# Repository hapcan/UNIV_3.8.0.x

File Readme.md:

UNIV 3.8.0.x
============

RGB LED Controller - 3 channel LED or 1 channel RGB LED controller 5A per channel @12-24V for DIN rail

Device webpage: http://hapcan.com/devices/universal/univ_3/univ_3-8-0-x/

Hardware created in Eagle PCB Software http://www.cadsoftusa.com/

Firmware created in Microchip MPLAB http://www.microchip.com/mplabide/ in assembly language

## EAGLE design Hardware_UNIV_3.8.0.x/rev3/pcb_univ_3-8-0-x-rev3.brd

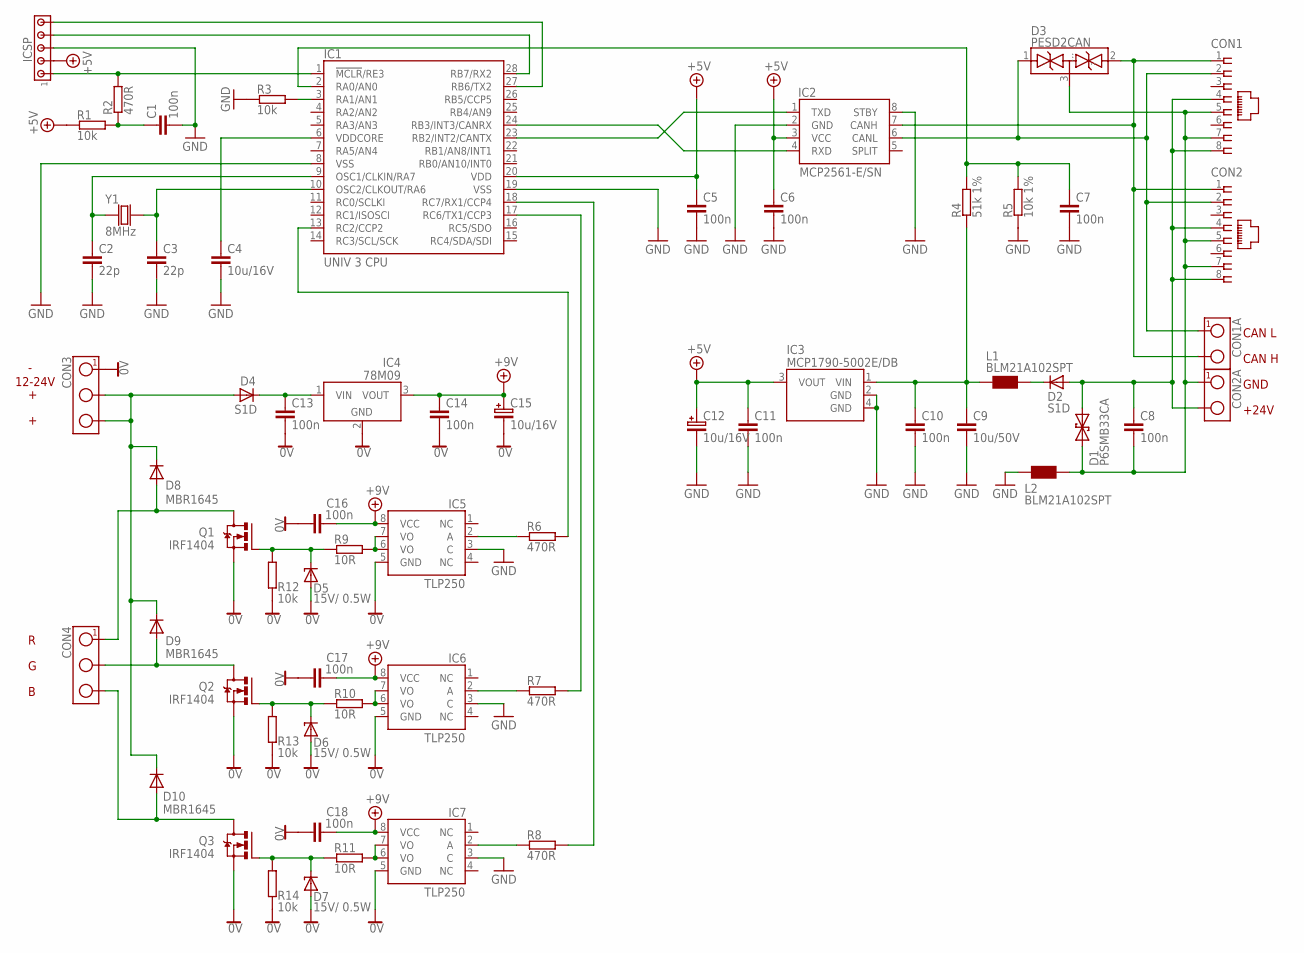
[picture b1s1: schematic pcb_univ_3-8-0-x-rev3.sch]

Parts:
C1, C5, C6, C7, C8, C10, C11, C13, C14, C16, C17, C18: 100n; 0805
C2, C3: 22p; 0805
C4: 10u/16V; 0805
C9: 10u/50V; 1210
C12, C15: 10u/16V; SMC_B
CON1, CON2: RJ45-SOCKET; RJ45-PCB-SOCKET
CON1A, CON2A: TERMINAL-2; ARK2-5X10,5MM
CON3, CON4: TERMINAL-3; ARK3-5X10.5MM
D1: P6SMB33CA; DO-214_TRANSIL2
D2, D4: S1D; DO-214
D3: PESD2CAN; SOT-23
D5, D6, D7: 15V/ 0.5W; SOD-80
D8, D9, D10: MBR1645; TO220V-2
IC1: UNIV 3 CPU; UNIV3CPU
IC2: MCP2561-E/SN; SO-08
IC3: MCP1790-5002E/DB; SOT-223
IC4: 78M09; TO-252
IC5, IC6, IC7: TLP250; DIL-08W
ICSP: HEADER5; SIP-5
L1, L2: BLM21A102SPT; 0805
Q1, Q2, Q3: IRF1404; TO220V
R1, R3, R12, R13, R14: 10k; 0805
R2, R6, R7, R8: 470R; 0805
R4: 51k 1%; 0805
R5: 10k 1%; 0805
R9, R10, R11: 10R; 0805
Y1: 8MHz; CRYSTAL-HC49V

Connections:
0V: C13.2, C14.2, C15.- (2), C16.1, C17.1, C18.1, CON3.1, D5.A, D6.A, D7.A, IC4.2 (GND), IC5.5 (GND), IC6.5 (GND), IC7.5 (GND), Q1.3 (S), Q2.3 (S), Q3.3 (S), R12.1, R13.1, R14.1
+5V: C5.1, C6.1, C11.1, C12.+ (1), IC1.20 (VDD), IC2.3 (VCC), IC3.3 (VOUT), ICSP.2, R1.1
+9V: C14.1, C15.+ (1), C16.2, C17.2, C18.2, IC4.3 (VOUT), IC5.8 (VCC), IC6.8 (VCC), IC7.8 (VCC)
GND: C1.2, C2.2, C3.2, C4.2, C5.2, C6.2, C7.2, C9.2, C10.2, C11.2, C12.- (2), IC1.8 (VSS), IC1.19 (VSS), IC2.2 (GND), IC2.8 (STBY), IC3.2 (GND), IC3.4 (GND), IC5.3 (C), IC6.3 (C), IC7.3 (C), ICSP.3, L2.1, R3.1, R5.1
unnamed: CON3.2, CON3.3, D4.A, D8.1 (C), D9.1 (C), D10.1 (C)
unnamed: IC1.24 (RB3/INT3/CANRX), IC2.4 (RXD)
unnamed: IC1.23 (RB2/INT2/CANTX), IC2.1 (TXD)
unnamed: CON1.1, CON1A.2, CON2.1, D3.2 (..), IC2.7 (CANH)
unnamed: IC5.6 (VO), IC5.7 (VO), R9.2
unnamed: IC6.6 (VO), IC6.7 (VO), R10.2
unnamed: C1.1, R1.2, R2.1
unnamed: IC1.1 (!MCLR!/RE3), ICSP.1, R2.2
unnamed: C8.1, CON1.4, CON1.8, CON2.4, CON2.8, CON2A.2, D1.C (2), D2.A
unnamed: IC1.28 (RB7/RX2), ICSP.4
unnamed: IC6.2 (A), R7.1
unnamed: IC1.3 (RA1/AN1), R3.2
unnamed: C13.1, D4.C, IC4.1 (VIN)
unnamed: IC1.27 (RB6/TX2), ICSP.5
unnamed: C3.1, IC1.10 (OSC2/CLKOUT/RA6), Y1.2
unnamed: C7.1, IC1.2 (RA0/AN0), R4.2, R5.2
unnamed: C9.1, C10.1, IC3.1 (VIN), L1.1, R4.1
unnamed: IC5.2 (A), R6.1
unnamed: IC1.13 (RC2/CCP2), R6.2
unnamed: IC1.17 (RC6/TX1/CCP3), R7.2
unnamed: IC1.18 (RC7/RX1/CCP4), R8.2
unnamed: C8.2, CON1.5, CON1.7, CON2.5, CON2.7, CON2A.1, D1.A (1), D3.3 (...), L2.2
unnamed: CON4.2, D9.3 (A), Q2.2 (D)
unnamed: D6.C, Q2.1 (G), R10.1, R13.2
unnamed: CON1.2, CON1A.1, CON2.2, D3.1 (.), IC2.6 (CANL)
unnamed: IC7.6 (VO), IC7.7 (VO), R11.2
unnamed: IC7.2 (A), R8.1
unnamed: D5.C, Q1.1 (G), R9.1, R12.2
unnamed: CON4.1, D8.3 (A), Q1.2 (D)
unnamed: CON4.3, D10.3 (A), Q3.2 (D)
unnamed: D7.C, Q3.1 (G), R11.1, R14.2
unnamed: C2.1, IC1.9 (OSC1/CLKIN/RA7), Y1.1
unnamed: C4.1, IC1.6 (VDDCORE)
unnamed: D2.C, L1.2

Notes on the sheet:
CAN L
CAN H
GND
+24V
12-24V

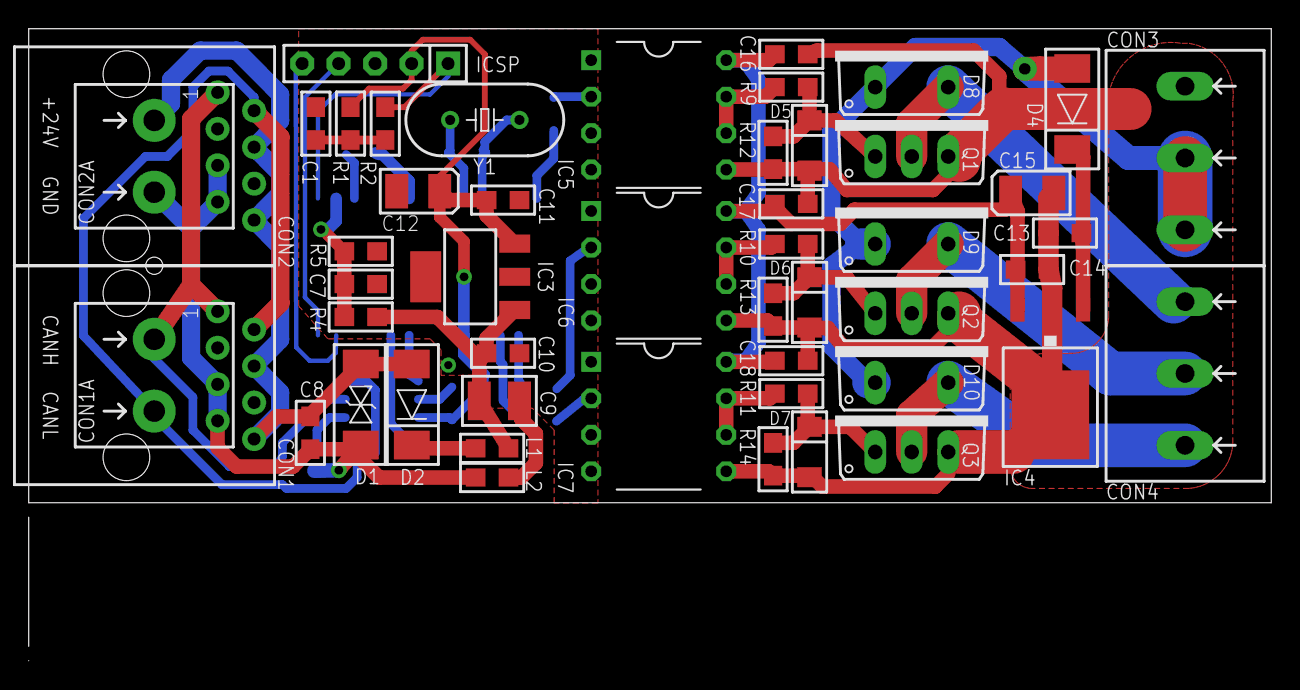
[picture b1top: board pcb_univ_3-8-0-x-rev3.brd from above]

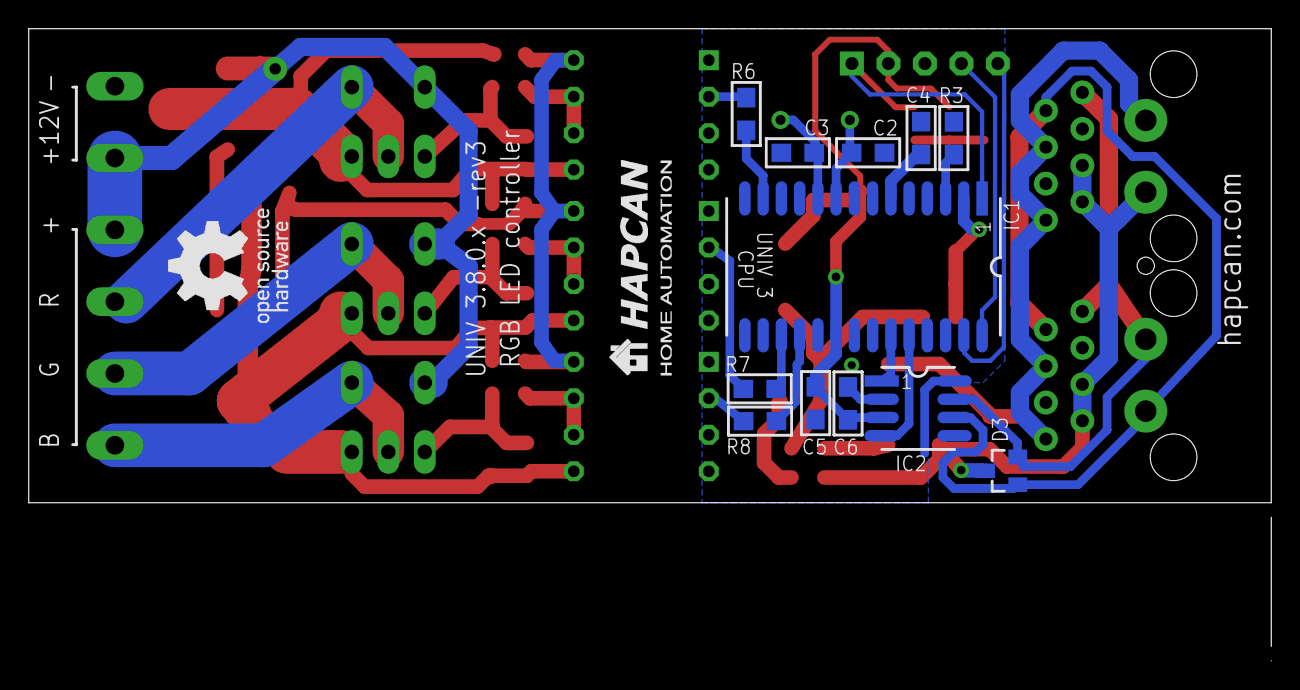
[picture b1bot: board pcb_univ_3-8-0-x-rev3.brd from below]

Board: 2 copper layers, 86.5 x 44.0 mm, 62 parts (12 on the bottom side), 38 nets.

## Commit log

2014-01-19 hardware revision 1
2014-01-24 firmware revision 0
2015-03-02 hardware revision 2
2015-08-22 hardware revision 3
2015-08-22 Revert "hardware revision 3"
    This reverts commit d9c47e6ec6357fc9da491421f110c58338fb49fe.
2015-11-08 firmware UNIV 3.8.0.0 revision 1
2016-12-30 firmware UNIV 3.8.0.0 revision 2
2022-11-15 firmware UNIV 3.8.0.0 revision 3
2022-11-15 MIT license
2026-01-19 hardware UNIV 3.8.0.x revision 3
